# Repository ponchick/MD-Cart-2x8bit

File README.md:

# MD-Cart-2x8bit

A KiCad project for a Sega Mega Drive/Genesis cartridge PCB. Designed to use two standard 8-bit 32-pin ROMs to form a 16-bit ROM bus.

## Hardware Requirements

Most parallel ROMs in DIP-32 packages with 8-bit memory organization should work. For EEPROM/Flash chips, solder jumper pins 1-2; for EPROM chips, solder pins 2-3.

### Compatible ROM Chips

The following DIP-32 8-bit *ROM chips have been tested and confirmed working with this design:

| Chip Model | Capacity | Organization | Jumpers |
|------------|----------|--------------|---------|
| ST M27C1001 | 128 KB | 1 Mbit × 8 | 2-3 |
| Winbond W27C020 | 256 KB | 2 Mbit × 8 | 1-2 |
| AMIC A29040B | 512 KB | 4 Mbit × 8 | 1-2 |
| SST SST39SF040 | 512 KB | 4 Mbit × 8 | 1-2 |
| ST M27C801 | 1 MB | 8 Mbit × 8 | 2-3 |

## Scripts

### split_msb_lsb.py

Splits a 16-bit binary file into upper and lower byte files for programming into two separate 8-bit ROMs. Supports big-endian (default for Motorola 68000) and little-endian byte order.

**Requirements:** Python 3.6 or higher. Optional: `libarchive-c` for archive format support.

#### Usage

```bash
python3 scripts/split_msb_lsb.py <filename> [options]
```

#### Options

- `filename` (required)
  - Input binary file or archive (.7z, .zip, .rar) to split
  - If an archive is provided, the first file found will be processed

- `--little-endian`
  - Use little-endian byte order instead of big-endian
  - Default: big-endian (Motorola 68000 standard)

- `-f, --force`
  - Overwrite existing output files without prompting
  - Default: prompt for confirmation if output files exist

- `-o, --output PREFIX`
  - Specify output filename prefix
  - Default: uses input filename as base
  - If `PREFIX` is an existing directory, files are saved there with original filename
  - Output files are named: `<prefix>.lower.bin` and `<prefix>.upper.bin`

- `--odd-byte {skip,lower,upper,error}`
  - Action to take when input file has odd number of bytes:
    - `error` (default): Print error and exit
    - `skip`: Skip the odd byte with a warning
    - `lower`: Add the odd byte to the lower byte file
    - `upper`: Add the odd byte to the upper byte file

#### Examples

```bash
# Basic usage (big-endian)
python3 scripts/split_msb_lsb.py rom.bin

# Little-endian byte order
python3 scripts/split_msb_lsb.py rom.bin --little-endian

# Specify output prefix
python3 scripts/split_msb_lsb.py rom.bin -o output/myrom

# Process archive and force overwrite
python3 scripts/split_msb_lsb.py game.zip -f

# Handle odd byte by adding to lower file
python3 scripts/split_msb_lsb.py rom.bin --odd-byte lower
```

#### Output

The script generates two files:

- `<prefix>.lower.bin` - Contains the lower (LSB) bytes for the first ROM
- `<prefix>.upper.bin` - Contains the upper (MSB) bytes for the second ROM

#### Archive Support

Archive format support requires `libarchive-c`:

```bash
pip install libarchive-c
```

Supported archive formats: `.7z`, `.zip`, `.rar`

## License

- Hardware: CERN Open Hardware Licence Version 2 - Permissive (CERN-OHL-P)
- Software: MIT License

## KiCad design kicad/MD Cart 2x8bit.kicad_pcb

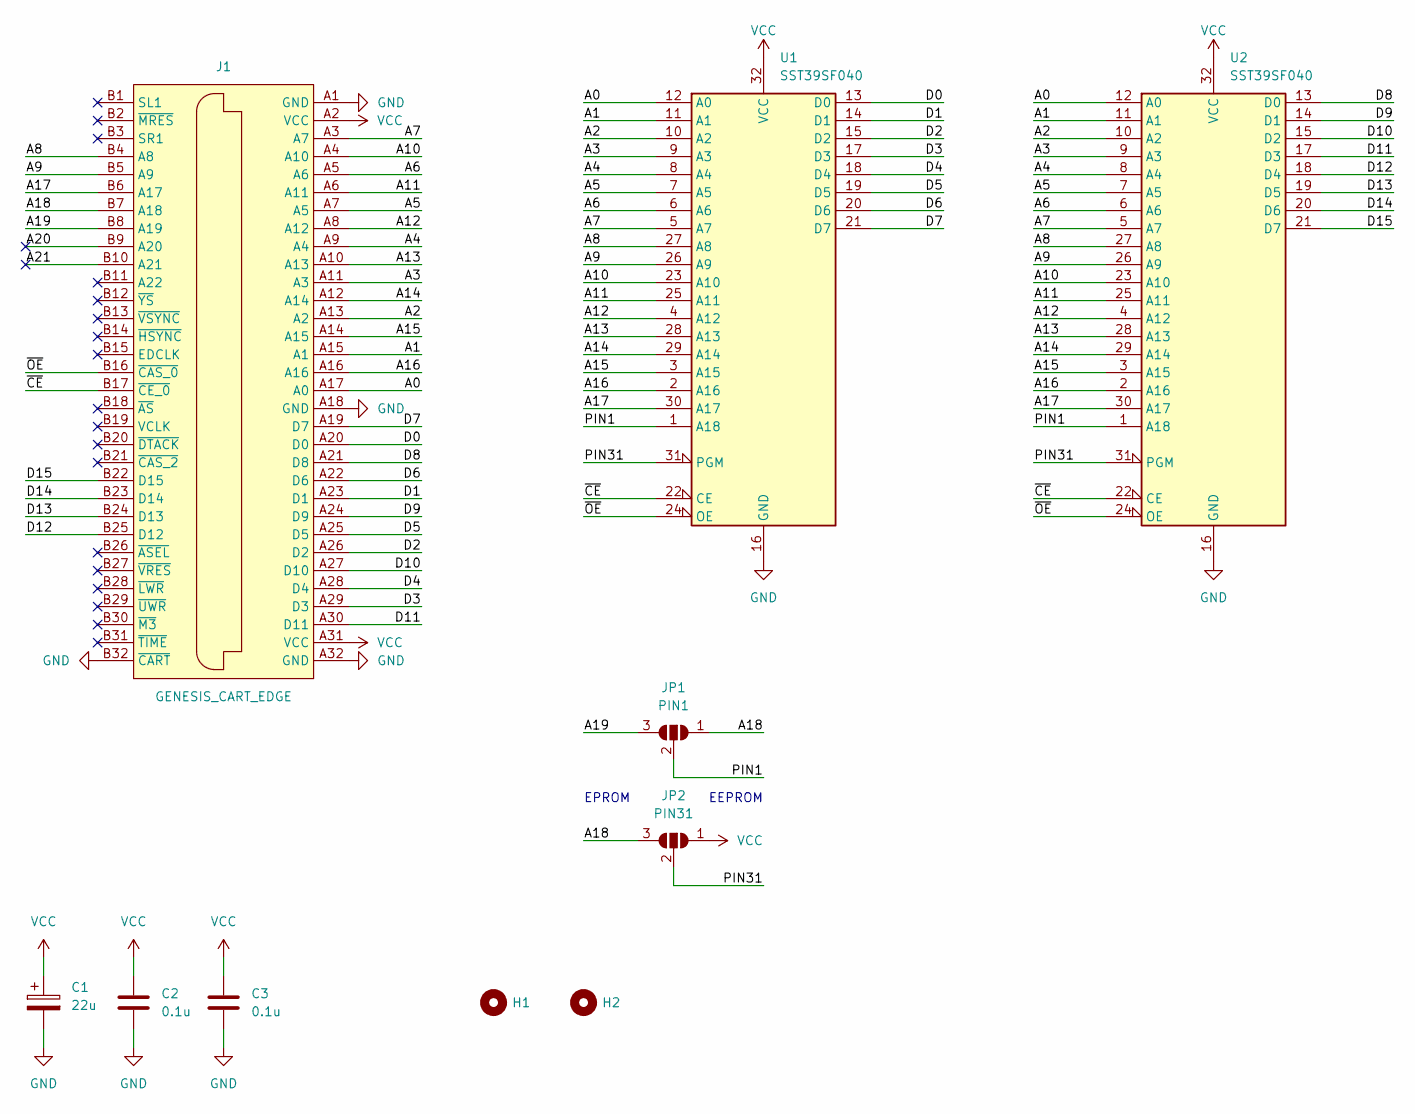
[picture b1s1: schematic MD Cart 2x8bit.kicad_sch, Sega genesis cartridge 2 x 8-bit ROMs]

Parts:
C1: 22u; CP_Radial_D5.0mm_P2.50mm
C2, C3: 0.1u; C_Disc_D4.3mm_W1.9mm_P5.00mm
H1, H2: HOLE_6.2
J1: GENESIS_CART_EDGE
JP1: PIN1; SolderJumper-3
JP2: PIN31; SolderJumper-3
U1, U2: SST39SF040; DIP-32_W15.24mm_Socket

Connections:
/A0: J1.A17 (A0), U1.12 (A0), U2.12 (A0)
/A1: J1.A15 (A1), U1.11 (A1), U2.11 (A1)
/A2: J1.A13 (A2), U1.10 (A2), U2.10 (A2)
/A3: J1.A11 (A3), U1.9 (A3), U2.9 (A3)
/A4: J1.A9 (A4), U1.8 (A4), U2.8 (A4)
/A5: J1.A7 (A5), U1.7 (A5), U2.7 (A5)
/A6: J1.A5 (A6), U1.6 (A6), U2.6 (A6)
/A7: J1.A3 (A7), U1.5 (A7), U2.5 (A7)
/A8: J1.B4 (A8), U1.27 (A8), U2.27 (A8)
/A9: J1.B5 (A9), U1.26 (A9), U2.26 (A9)
/A10: J1.A4 (A10), U1.23 (A10), U2.23 (A10)
/A11: J1.A6 (A11), U1.25 (A11), U2.25 (A11)
/A12: J1.A8 (A12), U1.4 (A12), U2.4 (A12)
/A13: J1.A10 (A13), U1.28 (A13), U2.28 (A13)
/A14: J1.A12 (A14), U1.29 (A14), U2.29 (A14)
/A15: J1.A14 (A15), U1.3 (A15), U2.3 (A15)
/A16: J1.A16, U1.2 (A16), U2.2 (A16)
/A17: J1.B6 (A17), U1.30 (A17), U2.30 (A17)
/A18: J1.B7 (A18), JP1.1 (A), JP2.3 (B)
/A19: J1.B8 (A19), JP1.3 (B)
/A20: J1.B9 (A20)
/A21: J1.B10 (A21)
/D0: J1.A20 (D0), U1.13 (D0)
/D1: J1.A23 (D1), U1.14 (D1)
/D2: J1.A26 (D2), U1.15 (D2)
/D3: J1.A29 (D3), U1.17 (D3)
/D4: J1.A28 (D4), U1.18 (D4)
/D5: J1.A25 (D5), U1.19 (D5)
/D6: J1.A22 (D6), U1.20 (D6)
/D7: J1.A19 (D7), U1.21 (D7)
/D8: J1.A21 (D8), U2.13 (D0)
/D9: J1.A24 (D9), U2.14 (D1)
/D10: J1.A27 (D10), U2.15 (D2)
/D11: J1.A30 (D11), U2.17 (D3)
/D12: J1.B25 (D12), U2.18 (D4)
/D13: J1.B24 (D13), U2.19 (D5)
/D14: J1.B23 (D14), U2.20 (D6)
/D15: J1.B22 (D15), U2.21 (D7)
/PIN1: JP1.2 (C), U1.1 (A18), U2.1 (A18)
/PIN31: JP2.2 (C), U1.31 (PGM), U2.31 (PGM)
/~CE: J1.B17 (~CE_0), U1.22 (CE), U2.22 (CE)
/~OE: J1.B16 (~CAS_0), U1.24 (OE), U2.24 (OE)
GND: C1.2, C2.1, C3.2, J1.A1 (GND), J1.A18 (GND), J1.A32 (GND), J1.B32 (~CART), U1.16 (GND), U2.16 (GND)
VCC: C1.1, C2.2, C3.1, J1.A2 (VCC), J1.A31 (VCC), JP2.1 (A), U1.32 (VCC), U2.32 (VCC)

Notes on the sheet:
EEPROM
EPROM

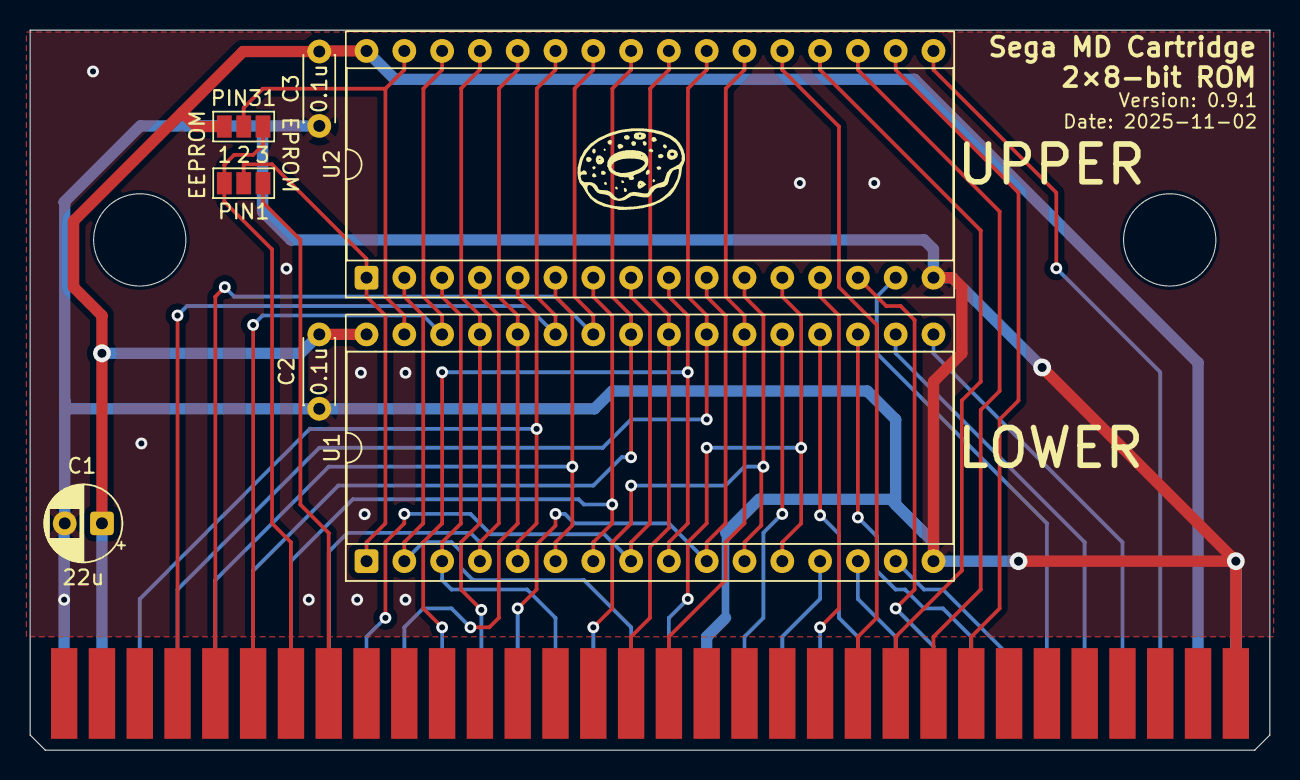
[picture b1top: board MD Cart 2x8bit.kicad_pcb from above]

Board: 2 copper layers, 83.3 x 48.4 mm, 11 parts (0 on the bottom side), 42 nets.

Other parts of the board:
LOGO#: LOGO; ponchick

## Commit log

2025-11-02 Initial release
